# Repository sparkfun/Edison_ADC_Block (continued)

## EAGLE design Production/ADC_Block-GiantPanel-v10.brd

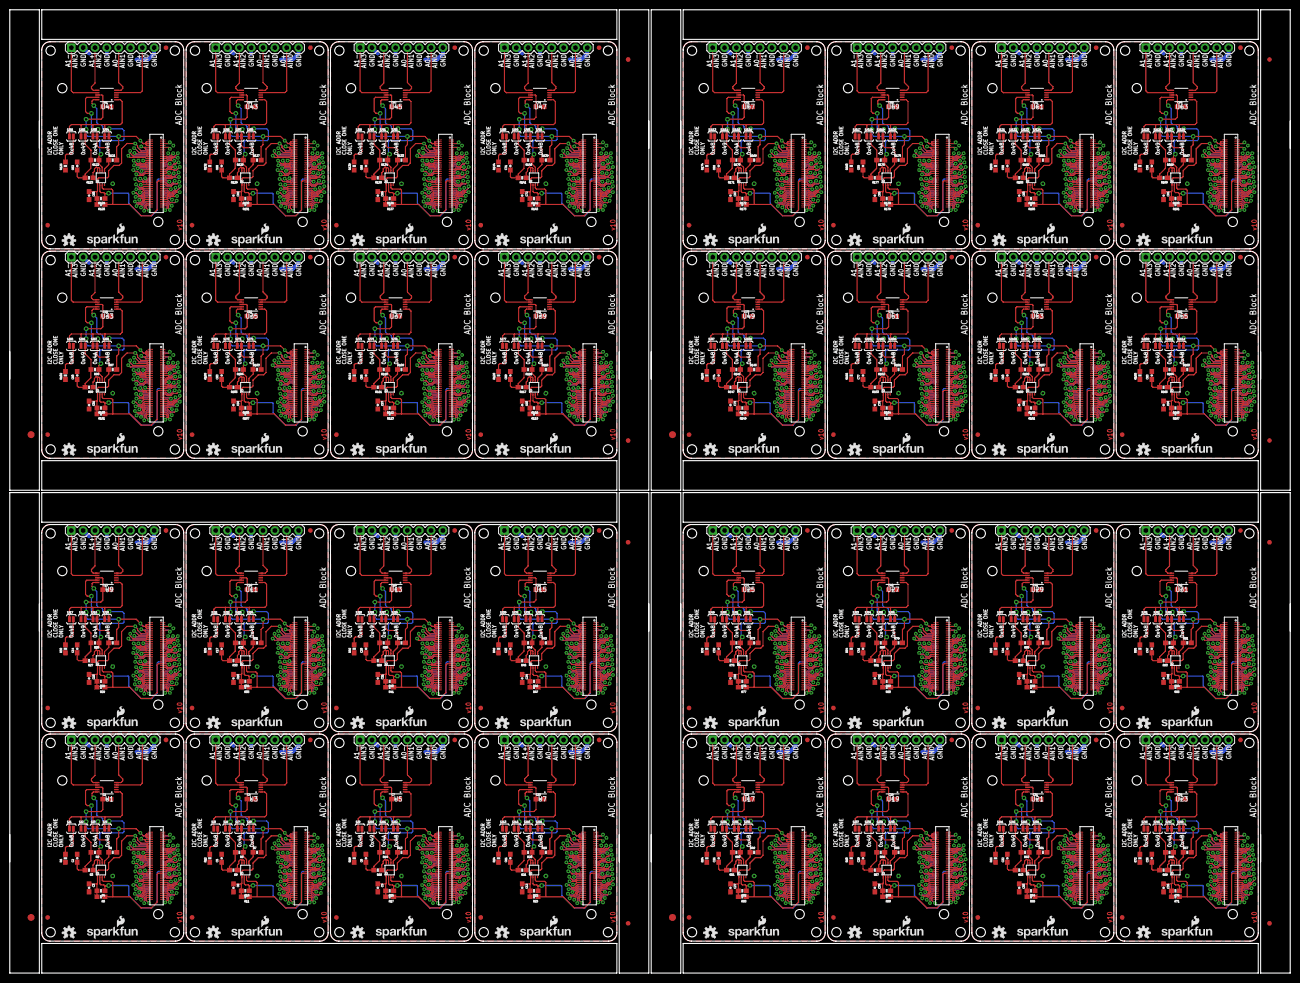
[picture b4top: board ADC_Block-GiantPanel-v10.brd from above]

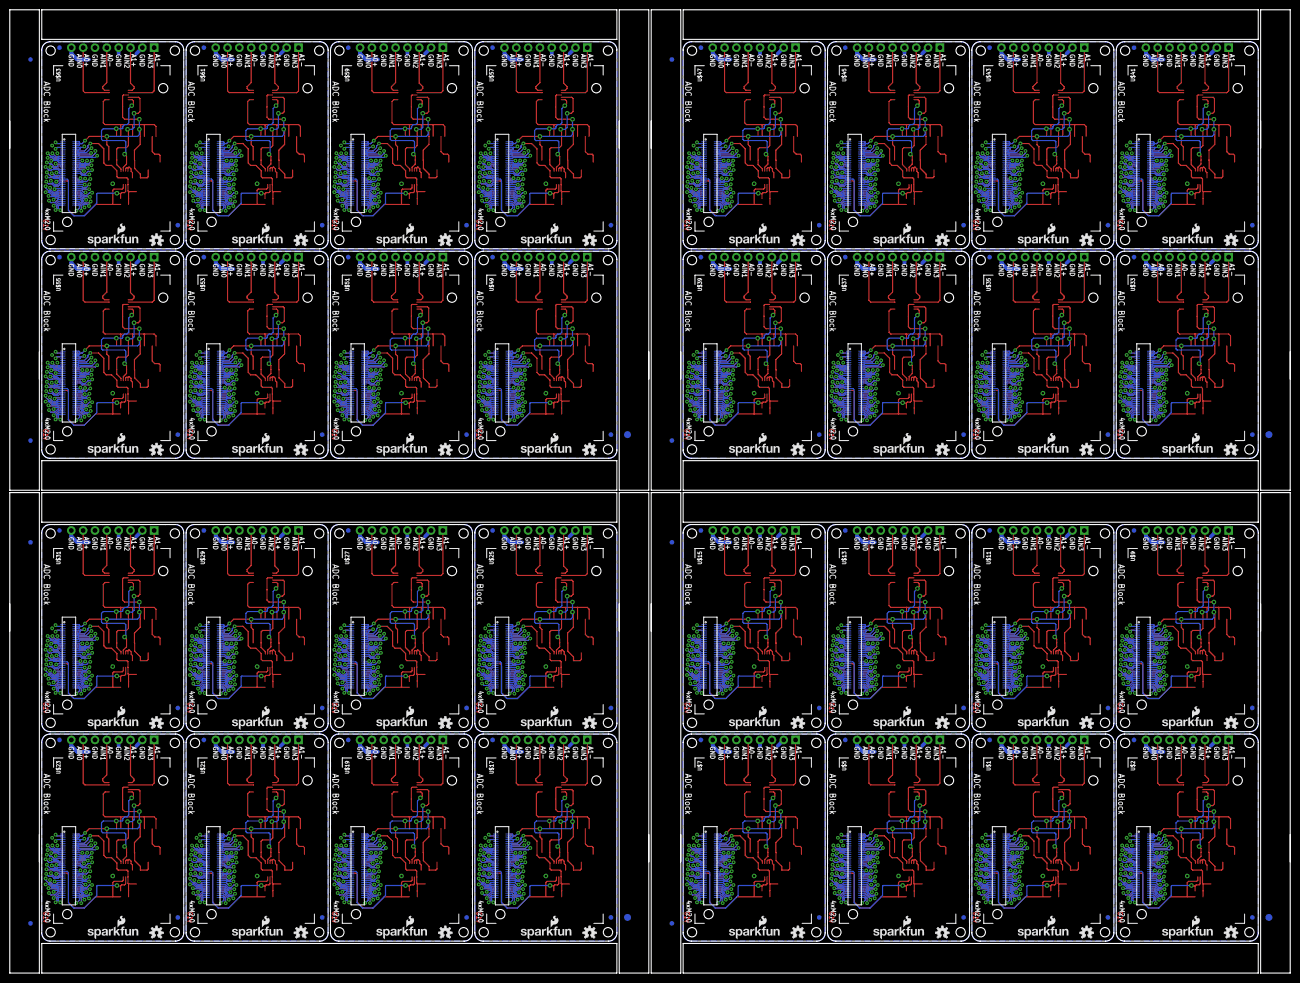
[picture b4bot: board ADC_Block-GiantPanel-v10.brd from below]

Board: 2 copper layers, 274.8 x 206.8 mm, 856 parts (204 on the bottom side), 2144 nets.

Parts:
C1, C2, C3, C4, C5, C6, C7, C8, C9, C10, C11, C12, C13, C14, C15, C16, C17, C18, C19, C20, C21, C22, C23, C24, C25, C26, C27, C28, C29, C30, C31, C32, C33, C34, C35, C36, C37, C38, C39, C40, C41, C42, C43, C44, C45, C46, C47, C48, C49, C50, C51, C52, C53, C54, C55, C56, C57, C58, C59, C60, C61, C62, C63, C64, C65, C66, C67, C68, C69, C70, C71, C72, C73, C74, C75, C76, C77, C78, C79, C80, C81, C82, C83, C84, C85, C86, C87, C88, C89, C90, C91, C92, C93, C94, C95, C96: 0.1uF; 0603-CAP
E$1, E$2, E$9, E$10, E$15, E$16, E$21, E$22: FIDUCIAL-1.5X3
E$3, E$4, E$5, E$6, E$7, E$8, E$11, E$12, E$13, E$14, E$17, E$18, E$19, E$20, E$23, E$24: FIDUCIAL-1X2
FID1, FID2, FID3, FID4, FID5, FID6, FID7, FID8, FID9, FID10, FID11, FID12, FID13, FID14, FID15, FID16, FID17, FID18, FID19, FID20, FID21, FID22, FID23, FID24, FID25, FID26, FID27, FID28, FID29, FID30, FID31, FID32, FID33, FID34, FID35, FID36, FID37, FID38, FID39, FID40, FID41, FID42, FID43, FID44, FID45, FID46, FID47, FID48, FID49, FID50, FID51, FID52, FID53, FID54, FID55, FID56, FID57, FID58, FID59, FID60, FID61, FID62, FID63, FID64, FID65, FID66, FID67, FID68, FID69, FID70, FID71, FID72, FID73, FID74, FID75, FID76, FID77, FID78, FID79, FID80, FID81, FID82, FID83, FID84, FID85, FID86, FID87, FID88, FID89, FID90, FID91, FID92, FID93, FID94, FID95, FID96, FID97, FID98, FID99, FID100, FID101, FID102, FID103, FID104, FID105, FID106, FID107, FID108, FID109, FID110, FID111, FID112, FID113, FID114, FID115, FID116, FID117, FID118, FID119, FID120, FID121, FID122, FID123, FID124, FID125, FID126, FID127, FID128: FIDUCIAL1X2; FIDUCIAL-1X2
JP1, JP2, JP3, JP4, JP5, JP6, JP7, JP8, JP9, JP10, JP11, JP12, JP13, JP14, JP15, JP16, JP17, JP18, JP19, JP20, JP21, JP22, JP23, JP24, JP25, JP26, JP27, JP28, JP29, JP30, JP31, JP32: 1X08
LOGO1, LOGO3, LOGO6, LOGO7, LOGO10, LOGO11, LOGO14, LOGO15, LOGO18, LOGO19, LOGO22, LOGO23, LOGO26, LOGO27, LOGO30, LOGO31, LOGO34, LOGO35, LOGO38, LOGO39, LOGO42, LOGO43, LOGO46, LOGO47, LOGO50, LOGO51, LOGO54, LOGO55, LOGO58, LOGO59, LOGO62, LOGO63, LOGO66, LOGO67, LOGO70, LOGO71, LOGO74, LOGO75, LOGO78, LOGO79, LOGO82, LOGO83, LOGO86, LOGO87, LOGO90, LOGO91, LOGO94, LOGO95, LOGO98, LOGO99, LOGO102, LOGO103, LOGO106, LOGO107, LOGO110, LOGO111, LOGO114, LOGO115, LOGO118, LOGO119, LOGO122, LOGO123, LOGO126, LOGO127: SFE_LOGO_NAME_FLAME.1_INCH; SFE_LOGO_NAME_FLAME_.1
LOGO2, LOGO4, LOGO5, LOGO8, LOGO9, LOGO12, LOGO13, LOGO16, LOGO17, LOGO20, LOGO21, LOGO24, LOGO25, LOGO28, LOGO29, LOGO32, LOGO33, LOGO36, LOGO37, LOGO40, LOGO41, LOGO44, LOGO45, LOGO48, LOGO49, LOGO52, LOGO53, LOGO56, LOGO57, LOGO60, LOGO61, LOGO64, LOGO65, LOGO68, LOGO69, LOGO72, LOGO73, LOGO76, LOGO77, LOGO80, LOGO81, LOGO84, LOGO85, LOGO88, LOGO89, LOGO92, LOGO93, LOGO96, LOGO97, LOGO100, LOGO101, LOGO104, LOGO105, LOGO108, LOGO109, LOGO112, LOGO113, LOGO116, LOGO117, LOGO120, LOGO121, LOGO124, LOGO125, LOGO128: OSHW-LOGOS; OSHW-LOGO-S
R1, R2, R7, R8, R13, R14, R19, R20, R25, R26, R31, R32, R37, R38, R43, R44, R49, R50, R55, R56, R61, R62, R67, R68, R73, R74, R79, R80, R85, R86, R91, R92, R97, R98, R103, R104, R109, R110, R115, R116, R121, R122, R127, R128, R133, R134, R139, R140, R145, R146, R151, R152, R157, R158, R163, R164, R169, R170, R175, R176, R181, R182, R187, R188: 10K; 0603-RES
R3, R9, R15, R21, R27, R33, R39, R45, R51, R57, R63, R69, R75, R81, R87, R93, R99, R105, R111, R117, R123, R129, R135, R141, R147, R153, R159, R165, R171, R177, R183, R189: 200k; 0603-RES
R4, R5, R10, R11, R16, R17, R22, R23, R28, R29, R34, R35, R40, R41, R46, R47, R52, R53, R58, R59, R64, R65, R70, R71, R76, R77, R82, R83, R88, R89, R94, R95, R100, R101, R106, R107, R112, R113, R118, R119, R124, R125, R130, R131, R136, R137, R142, R143, R148, R149, R154, R155, R160, R161, R166, R167, R172, R173, R178, R179, R184, R185, R190, R191: DNP; 0603-RES
R6, R12, R18, R24, R30, R36, R42, R48, R54, R60, R66, R72, R78, R84, R90, R96, R102, R108, R114, R120, R126, R132, R138, R144, R150, R156, R162, R168, R174, R180, R186, R192: 2.2k; 0603-RES
SJ1, SJ5, SJ9, SJ13, SJ17, SJ21, SJ25, SJ29, SJ33, SJ37, SJ41, SJ45, SJ49, SJ53, SJ57, SJ61, SJ65, SJ69, SJ73, SJ77, SJ81, SJ85, SJ89, SJ93, SJ97, SJ101, SJ105, SJ109, SJ113, SJ117, SJ121, SJ125: JUMPER-PAD-2-NC_BY_PASTE; PAD-JUMPER-2-NC_BY_PASTE_YES_SILK
SJ2, SJ3, SJ4, SJ6, SJ7, SJ8, SJ10, SJ11, SJ12, SJ14, SJ15, SJ16, SJ18, SJ19, SJ20, SJ22, SJ23, SJ24, SJ26, SJ27, SJ28, SJ30, SJ31, SJ32, SJ34, SJ35, SJ36, SJ38, SJ39, SJ40, SJ42, SJ43, SJ44, SJ46, SJ47, SJ48, SJ50, SJ51, SJ52, SJ54, SJ55, SJ56, SJ58, SJ59, SJ60, SJ62, SJ63, SJ64, SJ66, SJ67, SJ68, SJ70, SJ71, SJ72, SJ74, SJ75, SJ76, SJ78, SJ79, SJ80, SJ82, SJ83, SJ84, SJ86, SJ87, SJ88, SJ90, SJ91, SJ92, SJ94, SJ95, SJ96, SJ98, SJ99, SJ100, SJ102, SJ103, SJ104, SJ106, SJ107, SJ108, SJ110, SJ111, SJ112, SJ114, SJ115, SJ116, SJ118, SJ119, SJ120, SJ122, SJ123, SJ124, SJ126, SJ127, SJ128: JUMPER-PAD-2-NOYES_SILK; PAD-JUMPER-2-NO_YES_SILK
U1, U3, U5, U7, U9, U11, U13, U15, U17, U19, U21, U23, U25, U27, U29, U31, U33, U35, U37, U39, U41, U43, U45, U47, U49, U51, U53, U55, U57, U59, U61, U63: ADS1015; MSOP10
U2, U4, U6, U8, U10, U12, U14, U16, U18, U20, U22, U24, U26, U28, U30, U32, U34, U36, U38, U40, U42, U44, U46, U48, U50, U52, U54, U56, U58, U60, U62, U64: PCA9306; PCA9306DC-1:1
U$1, U$2, U$5, U$7, U$9, U$11, U$13, U$15, U$17, U$19, U$21, U$23, U$25, U$27, U$29, U$31, U$33, U$35, U$37, U$39, U$41, U$43, U$45, U$47, U$49, U$51, U$53, U$55, U$57, U$59, U$61, U$63: EDISON_CONNECTOR_FULLMOUNTING_HOLES; EDISON_DAUGHTER
U$3, U$4, U$6, U$8, U$10, U$12, U$14, U$16, U$18, U$20, U$22, U$24, U$26, U$28, U$30, U$32, U$34, U$36, U$38, U$40, U$42, U$44, U$46, U$48, U$50, U$52, U$54, U$56, U$58, U$60, U$62, U$64: EDISON_CONNECTOR_FULLHEADER; DF40C-70DP-0.4(51)

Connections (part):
1.8V: C3.1, R4.2, R5.2, U2.1, U$2.12, U$3.12
1.8V1: C6.1, R10.2, R11.2, U4.1, U$1.12, U$4.12
1.8V2: C9.1, R16.2, R17.2, U6.1, U$5.12, U$6.12
1.8V3: C12.1, R22.2, R23.2, U8.1, U$7.12, U$8.12
1.8V4: C15.1, R28.2, R29.2, U10.1, U$9.12, U$10.12
1.8V5: C18.1, R34.2, R35.2, U12.1, U$11.12, U$12.12
1.8V6: C21.1, R40.2, R41.2, U14.1, U$13.12, U$14.12
1.8V7: C24.1, R46.2, R47.2, U16.1, U$15.12, U$16.12
1.8V8: C27.1, R52.2, R53.2, U18.1, U$17.12, U$18.12
1.8V9: C30.1, R58.2, R59.2, U20.1, U$19.12, U$20.12
1.8V10: C33.1, R64.2, R65.2, U22.1, U$21.12, U$22.12
1.8V11: C36.1, R70.2, R71.2, U24.1, U$23.12, U$24.12
1.8V12: C39.1, R76.2, R77.2, U26.1, U$25.12, U$26.12
1.8V13: C42.1, R82.2, R83.2, U28.1, U$27.12, U$28.12
1.8V14: C45.1, R88.2, R89.2, U30.1, U$29.12, U$30.12
1.8V15: C48.1, R94.2, R95.2, U32.1, U$31.12, U$32.12
1.8V16: C51.1, R100.2, R101.2, U34.1, U$33.12, U$34.12
1.8V17: C54.1, R106.2, R107.2, U36.1, U$35.12, U$36.12
1.8V18: C57.1, R112.2, R113.2, U38.1, U$37.12, U$38.12
1.8V19: C60.1, R118.2, R119.2, U40.1, U$39.12, U$40.12
1.8V20: C63.1, R124.2, R125.2, U42.1, U$41.12, U$42.12
1.8V21: C66.1, R130.2, R131.2, U44.1, U$43.12, U$44.12
1.8V22: C69.1, R136.2, R137.2, U46.1, U$45.12, U$46.12
1.8V23: C72.1, R142.2, R143.2, U48.1, U$47.12, U$48.12
1.8V24: C75.1, R148.2, R149.2, U50.1, U$49.12, U$50.12
1.8V25: C78.1, R154.2, R155.2, U52.1, U$51.12, U$52.12
1.8V26: C81.1, R160.2, R161.2, U54.1, U$53.12, U$54.12
1.8V27: C84.1, R166.2, R167.2, U56.1, U$55.12, U$56.12
1.8V28: C87.1, R172.2, R173.2, U58.1, U$57.12, U$58.12
1.8V29: C90.1, R178.2, R179.2, U60.1, U$59.12, U$60.12
1.8V30: C93.1, R184.2, R185.2, U62.1, U$61.12, U$62.12
1.8V31: C96.1, R190.2, R191.2, U64.1, U$63.12, U$64.12
3.3V: U$2.8, U$2.10, U$3.8, U$3.10
3.3V1: U$1.8, U$1.10, U$4.8, U$4.10
3.3V2: U$5.8, U$5.10, U$6.8, U$6.10
3.3V3: U$7.8, U$7.10, U$8.8, U$8.10
3.3V4: U$9.8, U$9.10, U$10.8, U$10.10
3.3V5: U$11.8, U$11.10, U$12.8, U$12.10
3.3V6: U$13.8, U$13.10, U$14.8, U$14.10
3.3V7: U$15.8, U$15.10, U$16.8, U$16.10
3.3V8: U$17.8, U$17.10, U$18.8, U$18.10
3.3V9: U$19.8, U$19.10, U$20.8, U$20.10
3.3V10: U$21.8, U$21.10, U$22.8, U$22.10
3.3V11: U$23.8, U$23.10, U$24.8, U$24.10
3.3V12: U$25.8, U$25.10, U$26.8, U$26.10
3.3V13: U$27.8, U$27.10, U$28.8, U$28.10
3.3V14: U$29.8, U$29.10, U$30.8, U$30.10
3.3V15: U$31.8, U$31.10, U$32.8, U$32.10
3.3V16: U$33.8, U$33.10, U$34.8, U$34.10
3.3V17: U$35.8, U$35.10, U$36.8, U$36.10
3.3V18: U$37.8, U$37.10, U$38.8, U$38.10
3.3V19: U$39.8, U$39.10, U$40.8, U$40.10
3.3V20: U$41.8, U$41.10, U$42.8, U$42.10
3.3V21: U$43.8, U$43.10, U$44.8, U$44.10
3.3V22: U$45.8, U$45.10, U$46.8, U$46.10
3.3V23: U$47.8, U$47.10, U$48.8, U$48.10
3.3V24: U$49.8, U$49.10, U$50.8, U$50.10
3.3V25: U$51.8, U$51.10, U$52.8, U$52.10
3.3V26: U$53.8, U$53.10, U$54.8, U$54.10
3.3V27: U$55.8, U$55.10, U$56.8, U$56.10
3.3V28: U$57.8, U$57.10, U$58.8, U$58.10
3.3V29: U$59.8, U$59.10, U$60.8, U$60.10
3.3V30: U$61.8, U$61.10, U$62.8, U$62.10
3.3V31: U$63.8, U$63.10, U$64.8, U$64.10
A0+/AIN0: JP1.7, U1.4
A0+/AIN1: JP2.7, U3.4
A0+/AIN2: JP3.7, U5.4
A0+/AIN3: JP4.7, U7.4
A0+/AIN4: JP5.7, U9.4
A0+/AIN5: JP6.7, U11.4
A0+/AIN6: JP7.7, U13.4
A0+/AIN7: JP8.7, U15.4
A0+/AIN8: JP9.7, U17.4
A0+/AIN9: JP10.7, U19.4
A0+/AIN10: JP11.7, U21.4
A0+/AIN11: JP12.7, U23.4
A0+/AIN12: JP13.7, U25.4
A0+/AIN13: JP14.7, U27.4
A0+/AIN14: JP15.7, U29.4
A0+/AIN15: JP16.7, U31.4
A0+/AIN16: JP17.7, U33.4
A0+/AIN17: JP18.7, U35.4
A0+/AIN18: JP19.7, U37.4
A0+/AIN19: JP20.7, U39.4
A0+/AIN20: JP21.7, U41.4
A0+/AIN21: JP22.7, U43.4
A0+/AIN22: JP23.7, U45.4
A0+/AIN23: JP24.7, U47.4
A0+/AIN24: JP25.7, U49.4
A0+/AIN25: JP26.7, U51.4
A0+/AIN26: JP27.7, U53.4
A0+/AIN27: JP28.7, U55.4
A0+/AIN28: JP29.7, U57.4
A0+/AIN29: JP30.7, U59.4
A0+/AIN30: JP31.7, U61.4
A0+/AIN31: JP32.7, U63.4
A0-/AIN1: JP1.5, U1.5
A0-/AIN2: JP2.5, U3.5
A0-/AIN3: JP3.5, U5.5
A0-/AIN4: JP4.5, U7.5
A0-/AIN5: JP5.5, U9.5
A0-/AIN6: JP6.5, U11.5
A0-/AIN7: JP7.5, U13.5
A0-/AIN8: JP8.5, U15.5
A0-/AIN9: JP9.5, U17.5
A0-/AIN10: JP10.5, U19.5
A0-/AIN11: JP11.5, U21.5
A0-/AIN12: JP12.5, U23.5
A0-/AIN13: JP13.5, U25.5
A0-/AIN14: JP14.5, U27.5
A0-/AIN15: JP15.5, U29.5
A0-/AIN16: JP16.5, U31.5
A0-/AIN17: JP17.5, U33.5
A0-/AIN18: JP18.5, U35.5
A0-/AIN19: JP19.5, U37.5
A0-/AIN20: JP20.5, U39.5
A0-/AIN21: JP21.5, U41.5
A0-/AIN22: JP22.5, U43.5
A0-/AIN23: JP23.5, U45.5
A0-/AIN24: JP24.5, U47.5
A0-/AIN25: JP25.5, U49.5
A0-/AIN26: JP26.5, U51.5
A0-/AIN27: JP27.5, U53.5
A0-/AIN28: JP28.5, U55.5
A0-/AIN29: JP29.5, U57.5
A0-/AIN30: JP30.5, U59.5
A0-/AIN31: JP31.5, U61.5
A0-/AIN32: JP32.5, U63.5
A1+/AIN1: JP2.3, U3.6
A1+/AIN2: JP1.3, U1.6
A1+/AIN3: JP3.3, U5.6
A1+/AIN4: JP4.3, U7.6
A1+/AIN5: JP5.3, U9.6
A1+/AIN6: JP6.3, U11.6
A1+/AIN7: JP7.3, U13.6
A1+/AIN8: JP8.3, U15.6
A1+/AIN9: JP9.3, U17.6
A1+/AIN10: JP10.3, U19.6
A1+/AIN11: JP11.3, U21.6
A1+/AIN12: JP12.3, U23.6
A1+/AIN13: JP13.3, U25.6
A1+/AIN14: JP14.3, U27.6
A1+/AIN15: JP15.3, U29.6
A1+/AIN16: JP16.3, U31.6
A1+/AIN17: JP17.3, U33.6
A1+/AIN18: JP18.3, U35.6
A1+/AIN19: JP19.3, U37.6
A1+/AIN20: JP20.3, U39.6
A1+/AIN21: JP21.3, U41.6
A1+/AIN22: JP22.3, U43.6
A1+/AIN23: JP23.3, U45.6
A1+/AIN24: JP24.3, U47.6
A1+/AIN25: JP25.3, U49.6
A1+/AIN26: JP26.3, U51.6
A1+/AIN27: JP27.3, U53.6
A1+/AIN28: JP28.3, U55.6
A1+/AIN29: JP29.3, U57.6
A1+/AIN30: JP30.3, U59.6
A1+/AIN31: JP31.3, U61.6
A1+/AIN32: JP32.3, U63.6
A1-/AIN1: JP2.1, U3.7
A1-/AIN2: JP3.1, U5.7
A1-/AIN3: JP1.1, U1.7
A1-/AIN4: JP4.1, U7.7
A1-/AIN5: JP5.1, U9.7
A1-/AIN6: JP6.1, U11.7
A1-/AIN7: JP7.1, U13.7
A1-/AIN8: JP8.1, U15.7
A1-/AIN9: JP9.1, U17.7
A1-/AIN10: JP10.1, U19.7
A1-/AIN11: JP11.1, U21.7
A1-/AIN12: JP12.1, U23.7
A1-/AIN13: JP13.1, U25.7
A1-/AIN14: JP14.1, U27.7
A1-/AIN15: JP15.1, U29.7
A1-/AIN16: JP16.1, U31.7
A1-/AIN17: JP17.1, U33.7
A1-/AIN18: JP18.1, U35.7
A1-/AIN19: JP19.1, U37.7
A1-/AIN20: JP20.1, U39.7
A1-/AIN21: JP21.1, U41.7
A1-/AIN22: JP22.1, U43.7
A1-/AIN23: JP23.1, U45.7
A1-/AIN24: JP24.1, U47.7
A1-/AIN25: JP25.1, U49.7
A1-/AIN26: JP26.1, U51.7
A1-/AIN27: JP27.1, U53.7
A1-/AIN28: JP28.1, U55.7
A1-/AIN29: JP29.1, U57.7
A1-/AIN30: JP30.1, U59.7
A1-/AIN31: JP31.1, U61.7
A1-/AIN32: JP32.1, U63.7
ADDR: SJ1.1, SJ2.1, SJ3.1, SJ4.1, U1.1
ADDR1: SJ5.1, SJ6.1, SJ7.1, SJ8.1, U3.1
ADDR2: SJ9.1, SJ10.1, SJ11.1, SJ12.1, U5.1
ADDR3: SJ13.1, SJ14.1, SJ15.1, SJ16.1, U7.1
ADDR4: SJ17.1, SJ18.1, SJ19.1, SJ20.1, U9.1
ADDR5: SJ21.1, SJ22.1, SJ23.1, SJ24.1, U11.1
ADDR6: SJ25.1, SJ26.1, SJ27.1, SJ28.1, U13.1
ADDR7: SJ29.1, SJ30.1, SJ31.1, SJ32.1, U15.1
ADDR8: SJ33.1, SJ34.1, SJ35.1, SJ36.1, U17.1
ADDR9: SJ37.1, SJ38.1, SJ39.1, SJ40.1, U19.1
ADDR10: SJ41.1, SJ42.1, SJ43.1, SJ44.1, U21.1
ADDR11: SJ45.1, SJ46.1, SJ47.1, SJ48.1, U23.1
ADDR12: SJ49.1, SJ50.1, SJ51.1, SJ52.1, U25.1
ADDR13: SJ53.1, SJ54.1, SJ55.1, SJ56.1, U27.1
ADDR14: SJ57.1, SJ58.1, SJ59.1, SJ60.1, U29.1
ADDR15: SJ61.1, SJ62.1, SJ63.1, SJ64.1, U31.1
ADDR16: SJ65.1, SJ66.1, SJ67.1, SJ68.1, U33.1
ADDR17: SJ69.1, SJ70.1, SJ71.1, SJ72.1, U35.1
ADDR18: SJ73.1, SJ74.1, SJ75.1, SJ76.1, U37.1
ADDR19: SJ77.1, SJ78.1, SJ79.1, SJ80.1, U39.1
ADDR20: SJ81.1, SJ82.1, SJ83.1, SJ84.1, U41.1
ADDR21: SJ85.1, SJ86.1, SJ87.1, SJ88.1, U43.1
ADDR22: SJ89.1, SJ90.1, SJ91.1, SJ92.1, U45.1
ADDR23: SJ93.1, SJ94.1, SJ95.1, SJ96.1, U47.1
ADDR24: SJ97.1, SJ98.1, SJ99.1, SJ100.1, U49.1
ADDR25: SJ101.1, SJ102.1, SJ103.1, SJ104.1, U51.1
ADDR26: SJ105.1, SJ106.1, SJ107.1, SJ108.1, U53.1
ADDR27: SJ109.1, SJ110.1, SJ111.1, SJ112.1, U55.1
ADDR28: SJ113.1, SJ114.1, SJ115.1, SJ116.1, U57.1
ADDR29: SJ117.1, SJ118.1, SJ119.1, SJ120.1, U59.1
ADDR30: SJ121.1, SJ122.1, SJ123.1, SJ124.1, U61.1
ADDR31: SJ125.1, SJ126.1, SJ127.1, SJ128.1, U63.1
DCIN: U$2.14, U$3.14
DCIN1: U$1.14, U$4.14
DCIN2: U$5.14, U$6.14
DCIN3: U$7.14, U$8.14
DCIN4: U$9.14, U$10.14
DCIN5: U$11.14, U$12.14
DCIN6: U$13.14, U$14.14
DCIN7: U$15.14, U$16.14
DCIN8: U$17.14, U$18.14
DCIN9: U$19.14, U$20.14
DCIN10: U$21.14, U$22.14
DCIN11: U$23.14, U$24.14
DCIN12: U$25.14, U$26.14
DCIN13: U$27.14, U$28.14
DCIN14: U$29.14, U$30.14
DCIN15: U$31.14, U$32.14
DCIN16: U$33.14, U$34.14
DCIN17: U$35.14, U$36.14
DCIN18: U$37.14, U$38.14
DCIN19: U$39.14, U$40.14
DCIN20: U$41.14, U$42.14
DCIN21: U$43.14, U$44.14
DCIN22: U$45.14, U$46.14
DCIN23: U$47.14, U$48.14
DCIN24: U$49.14, U$50.14
DCIN25: U$51.14, U$52.14
DCIN26: U$53.14, U$54.14
DCIN27: U$55.14, U$56.14
DCIN28: U$57.14, U$58.14
DCIN29: U$59.14, U$60.14
DCIN30: U$61.14, U$62.14
DCIN31: U$63.14, U$64.14
FAULT: U$2.19, U$3.19
FAULT1: U$1.19, U$4.19
FAULT2: U$5.19, U$6.19
FAULT3: U$7.19, U$8.19
FAULT4: U$9.19, U$10.19
FAULT5: U$11.19, U$12.19
FAULT6: U$13.19, U$14.19
FAULT7: U$15.19, U$16.19
FAULT8: U$17.19, U$18.19
FAULT9: U$19.19, U$20.19
FAULT10: U$21.19, U$22.19
FAULT11: U$23.19, U$24.19
FAULT12: U$25.19, U$26.19
FAULT13: U$27.19, U$28.19
FAULT14: U$29.19, U$30.19
FAULT15: U$31.19, U$32.19
FAULT16: U$33.19, U$34.19
FAULT17: U$35.19, U$36.19
FAULT18: U$37.19, U$38.19
FAULT19: U$39.19, U$40.19
FAULT20: U$41.19, U$42.19
FAULT21: U$43.19, U$44.19
FAULT22: U$45.19, U$46.19
FAULT23: U$47.19, U$48.19
FAULT24: U$49.19, U$50.19
FAULT25: U$51.19, U$52.19
FAULT26: U$53.19, U$54.19
FAULT27: U$55.19, U$56.19
FAULT28: U$57.19, U$58.19
FAULT29: U$59.19, U$60.19
FAULT30: U$61.19, U$62.19
FAULT31: U$63.19, U$64.19
FW_RCVR: U$2.69, U$3.69
FW_RCVR1: U$1.69, U$4.69
FW_RCVR2: U$5.69, U$6.69
FW_RCVR3: U$7.69, U$8.69
FW_RCVR4: U$9.69, U$10.69
FW_RCVR5: U$11.69, U$12.69
FW_RCVR6: U$13.69, U$14.69
FW_RCVR7: U$15.69, U$16.69
FW_RCVR8: U$17.69, U$18.69
FW_RCVR9: U$19.69, U$20.69
FW_RCVR10: U$21.69, U$22.69
FW_RCVR11: U$23.69, U$24.69
FW_RCVR12: U$25.69, U$26.69
FW_RCVR13: U$27.69, U$28.69
FW_RCVR14: U$29.69, U$30.69
FW_RCVR15: U$31.69, U$32.69
FW_RCVR16: U$33.69, U$34.69
FW_RCVR17: U$35.69, U$36.69
FW_RCVR18: U$37.69, U$38.69
FW_RCVR19: U$39.69, U$40.69
FW_RCVR20: U$41.69, U$42.69
FW_RCVR21: U$43.69, U$44.69
FW_RCVR22: U$45.69, U$46.69
FW_RCVR23: U$47.69, U$48.69
FW_RCVR24: U$49.69, U$50.69
FW_RCVR25: U$51.69, U$52.69
FW_RCVR26: U$53.69, U$54.69
FW_RCVR27: U$55.69, U$56.69
FW_RCVR28: U$57.69, U$58.69
FW_RCVR29: U$59.69, U$60.69
FW_RCVR30: U$61.69, U$62.69
FW_RCVR31: U$63.69, U$64.69
GND: C1.2, C2.2, C3.2, JP1.2, JP1.4, JP1.6, JP1.8, R6.1, U1.3, U2.4, U$2.1, U$2.5, U$2.9, U$2.11, U$2.13, U$2.15, U$3.1, U$3.5, U$3.9, U$3.11, U$3.13, U$3.15
GND1: C4.2, C5.2, C6.2, JP2.2, JP2.4, JP2.6, JP2.8, R12.1, U3.3, U4.4, U$1.1, U$1.5, U$1.9, U$1.11, U$1.13, U$1.15, U$4.1, U$4.5, U$4.9, U$4.11, U$4.13, U$4.15
GND2: C7.2, C8.2, C9.2, JP3.2, JP3.4, JP3.6, JP3.8, R18.1, U5.3, U6.4, U$5.1, U$5.5, U$5.9, U$5.11, U$5.13, U$5.15, U$6.1, U$6.5, U$6.9, U$6.11, U$6.13, U$6.15
GND3: C10.2, C11.2, C12.2, JP4.2, JP4.4, JP4.6, JP4.8, R24.1, U7.3, U8.4, U$7.1, U$7.5, U$7.9, U$7.11, U$7.13, U$7.15, U$8.1, U$8.5, U$8.9, U$8.11, U$8.13, U$8.15
GND4: C13.2, C14.2, C15.2, JP5.2, JP5.4, JP5.6, JP5.8, R30.1, U9.3, U10.4, U$9.1, U$9.5, U$9.9, U$9.11, U$9.13, U$9.15, U$10.1, U$10.5, U$10.9, U$10.11, U$10.13, U$10.15
GND5: C16.2, C17.2, C18.2, JP6.2, JP6.4, JP6.6, JP6.8, R36.1, U11.3, U12.4, U$11.1, U$11.5, U$11.9, U$11.11, U$11.13, U$11.15, U$12.1, U$12.5, U$12.9, U$12.11, U$12.13, U$12.15
GND6: C19.2, C20.2, C21.2, JP7.2, JP7.4, JP7.6, JP7.8, R42.1, U13.3, U14.4, U$13.1, U$13.5, U$13.9, U$13.11, U$13.13, U$13.15, U$14.1, U$14.5, U$14.9, U$14.11, U$14.13, U$14.15
GND7: C22.2, C23.2, C24.2, JP8.2, JP8.4, JP8.6, JP8.8, R48.1, U15.3, U16.4, U$15.1, U$15.5, U$15.9, U$15.11, U$15.13, U$15.15, U$16.1, U$16.5, U$16.9, U$16.11, U$16.13, U$16.15
GND8: C25.2, C26.2, C27.2, JP9.2, JP9.4, JP9.6, JP9.8, R54.1, U17.3, U18.4, U$17.1, U$17.5, U$17.9, U$17.11, U$17.13, U$17.15, U$18.1, U$18.5, U$18.9, U$18.11, U$18.13, U$18.15
GND9: C28.2, C29.2, C30.2, JP10.2, JP10.4, JP10.6, JP10.8, R60.1, U19.3, U20.4, U$19.1, U$19.5, U$19.9, U$19.11, U$19.13, U$19.15, U$20.1, U$20.5, U$20.9, U$20.11, U$20.13, U$20.15
GND10: C31.2, C32.2, C33.2, JP11.2, JP11.4, JP11.6, JP11.8, R66.1, U21.3, U22.4, U$21.1, U$21.5, U$21.9, U$21.11, U$21.13, U$21.15, U$22.1, U$22.5, U$22.9, U$22.11, U$22.13, U$22.15
GND11: C34.2, C35.2, C36.2, JP12.2, JP12.4, JP12.6, JP12.8, R72.1, U23.3, U24.4, U$23.1, U$23.5, U$23.9, U$23.11, U$23.13, U$23.15, U$24.1, U$24.5, U$24.9, U$24.11, U$24.13, U$24.15
GND12: C37.2, C38.2, C39.2, JP13.2, JP13.4, JP13.6, JP13.8, R78.1, U25.3, U26.4, U$25.1, U$25.5, U$25.9, U$25.11, U$25.13, U$25.15, U$26.1, U$26.5, U$26.9, U$26.11, U$26.13, U$26.15
GND13: C40.2, C41.2, C42.2, JP14.2, JP14.4, JP14.6, JP14.8, R84.1, U27.3, U28.4, U$27.1, U$27.5, U$27.9, U$27.11, U$27.13, U$27.15, U$28.1, U$28.5, U$28.9, U$28.11, U$28.13, U$28.15
GND14: C43.2, C44.2, C45.2, JP15.2, JP15.4, JP15.6, JP15.8, R90.1, U29.3, U30.4, U$29.1, U$29.5, U$29.9, U$29.11, U$29.13, U$29.15, U$30.1, U$30.5, U$30.9, U$30.11, U$30.13, U$30.15
GND15: C46.2, C47.2, C48.2, JP16.2, JP16.4, JP16.6, JP16.8, R96.1, U31.3, U32.4, U$31.1, U$31.5, U$31.9, U$31.11, U$31.13, U$31.15, U$32.1, U$32.5, U$32.9, U$32.11, U$32.13, U$32.15
GND16: C49.2, C50.2, C51.2, JP17.2, JP17.4, JP17.6, JP17.8, R102.1, U33.3, U34.4, U$33.1, U$33.5, U$33.9, U$33.11, U$33.13, U$33.15, U$34.1, U$34.5, U$34.9, U$34.11, U$34.13, U$34.15
GND17: C52.2, C53.2, C54.2, JP18.2, JP18.4, JP18.6, JP18.8, R108.1, U35.3, U36.4, U$35.1, U$35.5, U$35.9, U$35.11, U$35.13, U$35.15, U$36.1, U$36.5, U$36.9, U$36.11, U$36.13, U$36.15
GND18: C55.2, C56.2, C57.2, JP19.2, JP19.4, JP19.6, JP19.8, R114.1, U37.3, U38.4, U$37.1, U$37.5, U$37.9, U$37.11, U$37.13, U$37.15, U$38.1, U$38.5, U$38.9, U$38.11, U$38.13, U$38.15
GND19: C58.2, C59.2, C60.2, JP20.2, JP20.4, JP20.6, JP20.8, R120.1, U39.3, U40.4, U$39.1, U$39.5, U$39.9, U$39.11, U$39.13, U$39.15, U$40.1, U$40.5, U$40.9, U$40.11, U$40.13, U$40.15
GND20: C61.2, C62.2, C63.2, JP21.2, JP21.4, JP21.6, JP21.8, R126.1, U41.3, U42.4, U$41.1, U$41.5, U$41.9, U$41.11, U$41.13, U$41.15, U$42.1, U$42.5, U$42.9, U$42.11, U$42.13, U$42.15
GND21: C64.2, C65.2, C66.2, JP22.2, JP22.4, JP22.6, JP22.8, R132.1, U43.3, U44.4, U$43.1, U$43.5, U$43.9, U$43.11, U$43.13, U$43.15, U$44.1, U$44.5, U$44.9, U$44.11, U$44.13, U$44.15
GND22: C67.2, C68.2, C69.2, JP23.2, JP23.4, JP23.6, JP23.8, R138.1, U45.3, U46.4, U$45.1, U$45.5, U$45.9, U$45.11, U$45.13, U$45.15, U$46.1, U$46.5, U$46.9, U$46.11, U$46.13, U$46.15
GND23: C70.2, C71.2, C72.2, JP24.2, JP24.4, JP24.6, JP24.8, R144.1, U47.3, U48.4, U$47.1, U$47.5, U$47.9, U$47.11, U$47.13, U$47.15, U$48.1, U$48.5, U$48.9, U$48.11, U$48.13, U$48.15
GND24: C73.2, C74.2, C75.2, JP25.2, JP25.4, JP25.6, JP25.8, R150.1, U49.3, U50.4, U$49.1, U$49.5, U$49.9, U$49.11, U$49.13, U$49.15, U$50.1, U$50.5, U$50.9, U$50.11, U$50.13, U$50.15
GND25: C76.2, C77.2, C78.2, JP26.2, JP26.4, JP26.6, JP26.8, R156.1, U51.3, U52.4, U$51.1, U$51.5, U$51.9, U$51.11, U$51.13, U$51.15, U$52.1, U$52.5, U$52.9, U$52.11, U$52.13, U$52.15
GND26: C79.2, C80.2, C81.2, JP27.2, JP27.4, JP27.6, JP27.8, R162.1, U53.3, U54.4, U$53.1, U$53.5, U$53.9, U$53.11, U$53.13, U$53.15, U$54.1, U$54.5, U$54.9, U$54.11, U$54.13, U$54.15
GND27: C82.2, C83.2, C84.2, JP28.2, JP28.4, JP28.6, JP28.8, R168.1, U55.3, U56.4, U$55.1, U$55.5, U$55.9, U$55.11, U$55.13, U$55.15, U$56.1, U$56.5, U$56.9, U$56.11, U$56.13, U$56.15
GND28: C85.2, C86.2, C87.2, JP29.2, JP29.4, JP29.6, JP29.8, R174.1, U57.3, U58.4, U$57.1, U$57.5, U$57.9, U$57.11, U$57.13, U$57.15, U$58.1, U$58.5, U$58.9, U$58.11, U$58.13, U$58.15
GND29: C88.2, C89.2, C90.2, JP30.2, JP30.4, JP30.6, JP30.8, R180.1, U59.3, U60.4, U$59.1, U$59.5, U$59.9, U$59.11, U$59.13, U$59.15, U$60.1, U$60.5, U$60.9, U$60.11, U$60.13, U$60.15
GND30: C91.2, C92.2, C93.2, JP31.2, JP31.4, JP31.6, JP31.8, R186.1, U61.3, U62.4, U$61.1, U$61.5, U$61.9, U$61.11, U$61.13, U$61.15, U$62.1, U$62.5, U$62.9, U$62.11, U$62.13, U$62.15
GND31: C94.2, C95.2, C96.2, JP32.2, JP32.4, JP32.6, JP32.8, R192.1, U63.3, U64.4, U$63.1, U$63.5, U$63.9, U$63.11, U$63.13, U$63.15, U$64.1, U$64.5, U$64.9, U$64.11, U$64.13, U$64.15
GP1: U$1.48, U$4.48
GP2: U$1.42, U$4.42
GP3: U$1.34, U$4.34
GP4: U$1.32, U$4.32
GP5: U$1.30, U$4.30
GP6: U$1.28, U$4.28
GP7: U$1.26, U$4.26
GP8: U$1.25, U$4.25
GP9: U$1.24, U$4.24
GP10: U$5.48, U$6.48
GP11: U$5.42, U$6.42
GP12: U$5.34, U$6.34
GP12_PWM0: U$2.35, U$3.35
GP12_PWM1: U$1.35, U$4.35
GP12_PWM2: U$5.35, U$6.35
GP12_PWM3: U$7.35, U$8.35
GP12_PWM4: U$9.35, U$10.35
GP12_PWM5: U$11.35, U$12.35
GP12_PWM6: U$13.35, U$14.35
GP12_PWM7: U$15.35, U$16.35
GP12_PWM8: U$17.35, U$18.35
GP12_PWM9: U$19.35, U$20.35
GP12_PWM10: U$21.35, U$22.35
GP12_PWM11: U$23.35, U$24.35
GP12_PWM12: U$25.35, U$26.35
GP12_PWM13: U$27.35, U$28.35
GP12_PWM14: U$29.35, U$30.35
GP12_PWM15: U$31.35, U$32.35
GP12_PWM16: U$33.35, U$34.35
GP12_PWM17: U$35.35, U$36.35
GP12_PWM18: U$37.35, U$38.35
GP12_PWM19: U$39.35, U$40.35
GP12_PWM20: U$41.35, U$42.35
GP12_PWM21: U$43.35, U$44.35
GP12_PWM22: U$45.35, U$46.35
GP12_PWM23: U$47.35, U$48.35
GP12_PWM24: U$49.35, U$50.35
GP12_PWM25: U$51.35, U$52.35
GP12_PWM26: U$53.35, U$54.35
GP12_PWM27: U$55.35, U$56.35
GP12_PWM28: U$57.35, U$58.35
GP12_PWM29: U$59.35, U$60.35
GP12_PWM30: U$61.35, U$62.35
GP12_PWM31: U$63.35, U$64.35
GP13: U$5.32, U$6.32
GP13_PWM1: U$2.33, U$3.33
GP13_PWM2: U$1.33, U$4.33
GP13_PWM3: U$5.33, U$6.33
GP13_PWM4: U$7.33, U$8.33
GP13_PWM5: U$9.33, U$10.33
GP13_PWM6: U$11.33, U$12.33
GP13_PWM7: U$13.33, U$14.33
GP13_PWM8: U$15.33, U$16.33
GP13_PWM9: U$17.33, U$18.33
GP13_PWM10: U$19.33, U$20.33
GP13_PWM11: U$21.33, U$22.33
GP13_PWM12: U$23.33, U$24.33
GP13_PWM13: U$25.33, U$26.33
GP13_PWM14: U$27.33, U$28.33
GP13_PWM15: U$29.33, U$30.33
GP13_PWM16: U$31.33, U$32.33
GP13_PWM17: U$33.33, U$34.33
GP13_PWM18: U$35.33, U$36.33
GP13_PWM19: U$37.33, U$38.33
GP13_PWM20: U$39.33, U$40.33
GP13_PWM21: U$41.33, U$42.33
GP13_PWM22: U$43.33, U$44.33
GP13_PWM23: U$45.33, U$46.33
GP13_PWM24: U$47.33, U$48.33
GP13_PWM25: U$49.33, U$50.33
GP13_PWM26: U$51.33, U$52.33
GP13_PWM27: U$53.33, U$54.33
GP13_PWM28: U$55.33, U$56.33
GP13_PWM29: U$57.33, U$58.33
GP13_PWM30: U$59.33, U$60.33
GP13_PWM31: U$61.33, U$62.33
GP13_PWM32: U$63.33, U$64.33
GP14: U$2.48, U$3.48
GP15: U$2.42, U$3.42
GP16: U$5.30, U$6.30
GP17: U$5.28, U$6.28
GP18: U$5.26, U$6.26
GP19: U$5.25, U$6.25
GP19_I2C_1_SCL: R4.1, U2.2, U$2.41, U$3.41
GP19_I2C_1_SCL1: R10.1, U4.2, U$1.41, U$4.41
GP19_I2C_1_SCL2: R16.1, U6.2, U$5.41, U$6.41
GP19_I2C_1_SCL3: R22.1, U8.2, U$7.41, U$8.41
GP19_I2C_1_SCL4: R28.1, U10.2, U$9.41, U$10.41
GP19_I2C_1_SCL5: R34.1, U12.2, U$11.41, U$12.41
GP19_I2C_1_SCL6: R40.1, U14.2, U$13.41, U$14.41
GP19_I2C_1_SCL7: R46.1, U16.2, U$15.41, U$16.41
GP19_I2C_1_SCL8: R52.1, U18.2, U$17.41, U$18.41
GP19_I2C_1_SCL9: R58.1, U20.2, U$19.41, U$20.41
GP19_I2C_1_SCL10: R64.1, U22.2, U$21.41, U$22.41
GP19_I2C_1_SCL11: R70.1, U24.2, U$23.41, U$24.41
GP19_I2C_1_SCL12: R76.1, U26.2, U$25.41, U$26.41
GP19_I2C_1_SCL13: R82.1, U28.2, U$27.41, U$28.41
GP19_I2C_1_SCL14: R88.1, U30.2, U$29.41, U$30.41
GP19_I2C_1_SCL15: R94.1, U32.2, U$31.41, U$32.41
GP19_I2C_1_SCL16: R100.1, U34.2, U$33.41, U$34.41
GP19_I2C_1_SCL17: R106.1, U36.2, U$35.41, U$36.41
GP19_I2C_1_SCL18: R112.1, U38.2, U$37.41, U$38.41
GP19_I2C_1_SCL19: R118.1, U40.2, U$39.41, U$40.41
GP19_I2C_1_SCL20: R124.1, U42.2, U$41.41, U$42.41
GP19_I2C_1_SCL21: R130.1, U44.2, U$43.41, U$44.41
GP19_I2C_1_SCL22: R136.1, U46.2, U$45.41, U$46.41
GP19_I2C_1_SCL23: R142.1, U48.2, U$47.41, U$48.41
GP19_I2C_1_SCL24: R148.1, U50.2, U$49.41, U$50.41
GP19_I2C_1_SCL25: R154.1, U52.2, U$51.41, U$52.41
GP19_I2C_1_SCL26: R160.1, U54.2, U$53.41, U$54.41
GP19_I2C_1_SCL27: R166.1, U56.2, U$55.41, U$56.41
GP19_I2C_1_SCL28: R172.1, U58.2, U$57.41, U$58.41
GP19_I2C_1_SCL29: R178.1, U60.2, U$59.41, U$60.41
GP19_I2C_1_SCL30: R184.1, U62.2, U$61.41, U$62.41
GP19_I2C_1_SCL31: R190.1, U64.2, U$63.41, U$64.41
GP20: U$5.24, U$6.24
GP20_I2C_1_SDA: R5.1, U2.3, U$2.43, U$3.43
GP20_I2C_1_SDA1: R11.1, U4.3, U$1.43, U$4.43
GP20_I2C_1_SDA2: R17.1, U6.3, U$5.43, U$6.43
GP20_I2C_1_SDA3: R23.1, U8.3, U$7.43, U$8.43
GP20_I2C_1_SDA4: R29.1, U10.3, U$9.43, U$10.43
GP20_I2C_1_SDA5: R35.1, U12.3, U$11.43, U$12.43
GP20_I2C_1_SDA6: R41.1, U14.3, U$13.43, U$14.43
GP20_I2C_1_SDA7: R47.1, U16.3, U$15.43, U$16.43
GP20_I2C_1_SDA8: R53.1, U18.3, U$17.43, U$18.43
GP20_I2C_1_SDA9: R59.1, U20.3, U$19.43, U$20.43
GP20_I2C_1_SDA10: R65.1, U22.3, U$21.43, U$22.43
GP20_I2C_1_SDA11: R71.1, U24.3, U$23.43, U$24.43
GP20_I2C_1_SDA12: R77.1, U26.3, U$25.43, U$26.43
GP20_I2C_1_SDA13: R83.1, U28.3, U$27.43, U$28.43
GP20_I2C_1_SDA14: R89.1, U30.3, U$29.43, U$30.43
GP20_I2C_1_SDA15: R95.1, U32.3, U$31.43, U$32.43
GP20_I2C_1_SDA16: R101.1, U34.3, U$33.43, U$34.43
GP20_I2C_1_SDA17: R107.1, U36.3, U$35.43, U$36.43
GP20_I2C_1_SDA18: R113.1, U38.3, U$37.43, U$38.43
GP20_I2C_1_SDA19: R119.1, U40.3, U$39.43, U$40.43
GP20_I2C_1_SDA20: R125.1, U42.3, U$41.43, U$42.43
GP20_I2C_1_SDA21: R131.1, U44.3, U$43.43, U$44.43
GP20_I2C_1_SDA22: R137.1, U46.3, U$45.43, U$46.43
GP20_I2C_1_SDA23: R143.1, U48.3, U$47.43, U$48.43
GP20_I2C_1_SDA24: R149.1, U50.3, U$49.43, U$50.43
GP20_I2C_1_SDA25: R155.1, U52.3, U$51.43, U$52.43
GP20_I2C_1_SDA26: R161.1, U54.3, U$53.43, U$54.43
GP20_I2C_1_SDA27: R167.1, U56.3, U$55.43, U$56.43
GP20_I2C_1_SDA28: R173.1, U58.3, U$57.43, U$58.43
GP20_I2C_1_SDA29: R179.1, U60.3, U$59.43, U$60.43
GP20_I2C_1_SDA30: R185.1, U62.3, U$61.43, U$62.43
GP20_I2C_1_SDA31: R191.1, U64.3, U$63.43, U$64.43
GP21: U$7.48, U$8.48
GP22: U$7.42, U$8.42
GP23: U$7.34, U$8.34
GP24: U$7.32, U$8.32
GP25: U$7.30, U$8.30
GP26: U$7.28, U$8.28
GP27: U$7.26, U$8.26
GP27_I2C_6_SCL: U$2.45, U$3.45
GP27_I2C_6_SCL1: U$1.45, U$4.45
GP27_I2C_6_SCL2: U$5.45, U$6.45
GP27_I2C_6_SCL3: U$7.45, U$8.45
GP27_I2C_6_SCL4: U$9.45, U$10.45
GP27_I2C_6_SCL5: U$11.45, U$12.45
GP27_I2C_6_SCL6: U$13.45, U$14.45
GP27_I2C_6_SCL7: U$15.45, U$16.45
GP27_I2C_6_SCL8: U$17.45, U$18.45
GP27_I2C_6_SCL9: U$19.45, U$20.45
GP27_I2C_6_SCL10: U$21.45, U$22.45
GP27_I2C_6_SCL11: U$23.45, U$24.45
GP27_I2C_6_SCL12: U$25.45, U$26.45
GP27_I2C_6_SCL13: U$27.45, U$28.45
GP27_I2C_6_SCL14: U$29.45, U$30.45
GP27_I2C_6_SCL15: U$31.45, U$32.45
GP27_I2C_6_SCL16: U$33.45, U$34.45
GP27_I2C_6_SCL17: U$35.45, U$36.45
GP27_I2C_6_SCL18: U$37.45, U$38.45
GP27_I2C_6_SCL19: U$39.45, U$40.45
GP27_I2C_6_SCL20: U$41.45, U$42.45
GP27_I2C_6_SCL21: U$43.45, U$44.45
GP27_I2C_6_SCL22: U$45.45, U$46.45
GP27_I2C_6_SCL23: U$47.45, U$48.45
GP27_I2C_6_SCL24: U$49.45, U$50.45
GP27_I2C_6_SCL25: U$51.45, U$52.45
GP27_I2C_6_SCL26: U$53.45, U$54.45
GP27_I2C_6_SCL27: U$55.45, U$56.45
GP27_I2C_6_SCL28: U$57.45, U$58.45
GP27_I2C_6_SCL29: U$59.45, U$60.45
GP27_I2C_6_SCL30: U$61.45, U$62.45
GP27_I2C_6_SCL31: U$63.45, U$64.45
GP28: U$7.25, U$8.25
GP28_I2C_6_SDA: U$2.47, U$3.47
GP28_I2C_6_SDA1: U$1.47, U$4.47
GP28_I2C_6_SDA2: U$5.47, U$6.47
GP28_I2C_6_SDA3: U$7.47, U$8.47
GP28_I2C_6_SDA4: U$9.47, U$10.47
GP28_I2C_6_SDA5: U$11.47, U$12.47
GP28_I2C_6_SDA6: U$13.47, U$14.47
GP28_I2C_6_SDA7: U$15.47, U$16.47
GP28_I2C_6_SDA8: U$17.47, U$18.47
GP28_I2C_6_SDA9: U$19.47, U$20.47
GP28_I2C_6_SDA10: U$21.47, U$22.47
GP28_I2C_6_SDA11: U$23.47, U$24.47
GP28_I2C_6_SDA12: U$25.47, U$26.47
GP28_I2C_6_SDA13: U$27.47, U$28.47
GP28_I2C_6_SDA14: U$29.47, U$30.47
GP28_I2C_6_SDA15: U$31.47, U$32.47
GP28_I2C_6_SDA16: U$33.47, U$34.47
GP28_I2C_6_SDA17: U$35.47, U$36.47
GP28_I2C_6_SDA18: U$37.47, U$38.47
GP28_I2C_6_SDA19: U$39.47, U$40.47
GP28_I2C_6_SDA20: U$41.47, U$42.47
GP28_I2C_6_SDA21: U$43.47, U$44.47
GP28_I2C_6_SDA22: U$45.47, U$46.47
GP28_I2C_6_SDA23: U$47.47, U$48.47
GP28_I2C_6_SDA24: U$49.47, U$50.47
GP28_I2C_6_SDA25: U$51.47, U$52.47
GP28_I2C_6_SDA26: U$53.47, U$54.47
GP28_I2C_6_SDA27: U$55.47, U$56.47
GP28_I2C_6_SDA28: U$57.47, U$58.47
GP28_I2C_6_SDA29: U$59.47, U$60.47
GP28_I2C_6_SDA30: U$61.47, U$62.47
GP28_I2C_6_SDA31: U$63.47, U$64.47
GP29: U$7.24, U$8.24
GP30: U$9.48, U$10.48
GP31: U$9.42, U$10.42
GP32: U$9.34, U$10.34
GP33: U$9.32, U$10.32
GP34: U$9.30, U$10.30
GP35: U$9.28, U$10.28
GP36: U$9.26, U$10.26
GP37: U$9.25, U$10.25
GP38: U$9.24, U$10.24
GP39: U$11.48, U$12.48
GP40: U$11.42, U$12.42
GP40_I2S_2_CLK: U$2.52, U$3.52
GP40_I2S_2_CLK1: U$1.52, U$4.52
GP40_I2S_2_CLK2: U$5.52, U$6.52
GP40_I2S_2_CLK3: U$7.52, U$8.52
GP40_I2S_2_CLK4: U$9.52, U$10.52
GP40_I2S_2_CLK5: U$11.52, U$12.52
GP40_I2S_2_CLK6: U$13.52, U$14.52
GP40_I2S_2_CLK7: U$15.52, U$16.52
GP40_I2S_2_CLK8: U$17.52, U$18.52
GP40_I2S_2_CLK9: U$19.52, U$20.52
GP40_I2S_2_CLK10: U$21.52, U$22.52
GP40_I2S_2_CLK11: U$23.52, U$24.52
GP40_I2S_2_CLK12: U$25.52, U$26.52
GP40_I2S_2_CLK13: U$27.52, U$28.52
GP40_I2S_2_CLK14: U$29.52, U$30.52
GP40_I2S_2_CLK15: U$31.52, U$32.52
GP40_I2S_2_CLK16: U$33.52, U$34.52
GP40_I2S_2_CLK17: U$35.52, U$36.52
GP40_I2S_2_CLK18: U$37.52, U$38.52
GP40_I2S_2_CLK19: U$39.52, U$40.52
GP40_I2S_2_CLK20: U$41.52, U$42.52
GP40_I2S_2_CLK21: U$43.52, U$44.52
GP40_I2S_2_CLK22: U$45.52, U$46.52
GP40_I2S_2_CLK23: U$47.52, U$48.52
GP40_I2S_2_CLK24: U$49.52, U$50.52
GP40_I2S_2_CLK25: U$51.52, U$52.52
GP40_I2S_2_CLK26: U$53.52, U$54.52
GP40_I2S_2_CLK27: U$55.52, U$56.52
GP40_I2S_2_CLK28: U$57.52, U$58.52
GP40_I2S_2_CLK29: U$59.52, U$60.52
GP40_I2S_2_CLK30: U$61.52, U$62.52
GP40_I2S_2_CLK31: U$63.52, U$64.52
GP41: U$11.34, U$12.34
GP41_I2S_2_FS: U$2.54, U$3.54
GP41_I2S_2_FS1: U$1.54, U$4.54
GP41_I2S_2_FS2: U$5.54, U$6.54
GP41_I2S_2_FS3: U$7.54, U$8.54
GP41_I2S_2_FS4: U$9.54, U$10.54
GP41_I2S_2_FS5: U$11.54, U$12.54
GP41_I2S_2_FS6: U$13.54, U$14.54
GP41_I2S_2_FS7: U$15.54, U$16.54
GP41_I2S_2_FS8: U$17.54, U$18.54
GP41_I2S_2_FS9: U$19.54, U$20.54
GP41_I2S_2_FS10: U$21.54, U$22.54
GP41_I2S_2_FS11: U$23.54, U$24.54
GP41_I2S_2_FS12: U$25.54, U$26.54
GP41_I2S_2_FS13: U$27.54, U$28.54
GP41_I2S_2_FS14: U$29.54, U$30.54
GP41_I2S_2_FS15: U$31.54, U$32.54
GP41_I2S_2_FS16: U$33.54, U$34.54
GP41_I2S_2_FS17: U$35.54, U$36.54
GP41_I2S_2_FS18: U$37.54, U$38.54
GP41_I2S_2_FS19: U$39.54, U$40.54
GP41_I2S_2_FS20: U$41.54, U$42.54
GP41_I2S_2_FS21: U$43.54, U$44.54
GP41_I2S_2_FS22: U$45.54, U$46.54
GP41_I2S_2_FS23: U$47.54, U$48.54
GP41_I2S_2_FS24: U$49.54, U$50.54
GP41_I2S_2_FS25: U$51.54, U$52.54
GP41_I2S_2_FS26: U$53.54, U$54.54
GP41_I2S_2_FS27: U$55.54, U$56.54
GP41_I2S_2_FS28: U$57.54, U$58.54
GP41_I2S_2_FS29: U$59.54, U$60.54
GP41_I2S_2_FS30: U$61.54, U$62.54
GP41_I2S_2_FS31: U$63.54, U$64.54
GP42: U$11.32, U$12.32
GP42_I2S_2_RXD: U$2.50, U$3.50
GP42_I2S_2_RXD1: U$1.50, U$4.50
GP42_I2S_2_RXD2: U$5.50, U$6.50
GP42_I2S_2_RXD3: U$7.50, U$8.50
GP42_I2S_2_RXD4: U$9.50, U$10.50
GP42_I2S_2_RXD5: U$11.50, U$12.50
GP42_I2S_2_RXD6: U$13.50, U$14.50
GP42_I2S_2_RXD7: U$15.50, U$16.50
GP42_I2S_2_RXD8: U$17.50, U$18.50
GP42_I2S_2_RXD9: U$19.50, U$20.50
GP42_I2S_2_RXD10: U$21.50, U$22.50
GP42_I2S_2_RXD11: U$23.50, U$24.50
GP42_I2S_2_RXD12: U$25.50, U$26.50
GP42_I2S_2_RXD13: U$27.50, U$28.50
GP42_I2S_2_RXD14: U$29.50, U$30.50
GP42_I2S_2_RXD15: U$31.50, U$32.50
GP42_I2S_2_RXD16: U$33.50, U$34.50
GP42_I2S_2_RXD17: U$35.50, U$36.50
GP42_I2S_2_RXD18: U$37.50, U$38.50
GP42_I2S_2_RXD19: U$39.50, U$40.50
GP42_I2S_2_RXD20: U$41.50, U$42.50
GP42_I2S_2_RXD21: U$43.50, U$44.50
GP42_I2S_2_RXD22: U$45.50, U$46.50
GP42_I2S_2_RXD23: U$47.50, U$48.50
GP42_I2S_2_RXD24: U$49.50, U$50.50
GP42_I2S_2_RXD25: U$51.50, U$52.50
GP42_I2S_2_RXD26: U$53.50, U$54.50
GP42_I2S_2_RXD27: U$55.50, U$56.50
GP42_I2S_2_RXD28: U$57.50, U$58.50
GP42_I2S_2_RXD29: U$59.50, U$60.50
GP42_I2S_2_RXD30: U$61.50, U$62.50
GP42_I2S_2_RXD31: U$63.50, U$64.50
GP43: U$11.30, U$12.30
GP43_I2S_2_TXD: U$2.56, U$3.56
GP43_I2S_2_TXD1: U$1.56, U$4.56
GP43_I2S_2_TXD2: U$5.56, U$6.56
GP43_I2S_2_TXD3: U$7.56, U$8.56
GP43_I2S_2_TXD4: U$9.56, U$10.56
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
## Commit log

2014-08-06 Board ready for review
2014-08-06 Add version info
2014-08-06 Updated to new edison.lbr
2014-08-08 Incorporate review feedback
2014-08-11 Add fids
2014-08-12 Fix fids, remove weird name
2014-09-24 Added DCIN pin Renamed boards and moved name around clenaed up copper pours clenaed up dimensions and units.
2014-10-16 Chg pullups to 10k, update gnd and pwr traces, rev to 10
2014-10-17 Rev to 10, fix pwr, gnd, txt
2014-10-17 removed stray Bplace from Package
2014-10-17 Ready for reds.
    Changed some silk to make headers more clear.
    No known to-do list.
2014-10-21 created v10 panels
2015-01-08 made modifications to add a 3.3v reference voltage and power supply to measure potentiometers from. This will allow the block to be used in a stand alone mode.
2015-03-16 updated rev number
2015-03-16 added ground vias and removed right angle trace
2015-03-23 corrected issues in github
2015-04-01 Updating README and directory file name
2015-04-09 changing pour layers
2015-04-09 copper restrict changes
2015-04-13 added Bus selection to board
2015-04-13 added note to SCH
2015-04-28 made changes from github issues
2015-06-02 Chg silk for diff chl info
2015-06-10 Finalized silk for both side for diff chl info
2015-06-25 moved differential pair chart and added separation lines
2015-06-25 replaces output capacitor on the 3.3v regulator with 2.2uF
2015-07-20 fixed thermal issue preventing gnd pour to connect with pads
2015-07-20 updated part values
2015-08-05 created panel v20
2015-10-01 Updating README, adding license file
2015-10-27 Added resistor to output cap on LDO. Changed header to locking male header.
2015-10-28 Cleaned up traces. Moved revision notes on schematic.
2015-12-03 Changed R4 and R5 to DNP, which is how they were in v21.
2015-12-11 Moved pin 1 markers to outside packages on IC and Hirose connectors.
2015-12-11 Changed solder jumper to make I2C_6 default
2015-12-11 Added notes about PCB thickness and DRC rules
2015-12-14 Changed I2C back to bus 1 for default
2015-12-14 Updating .gitignore
2015-12-14 created panel v21
2016-05-05 Updating readme links
